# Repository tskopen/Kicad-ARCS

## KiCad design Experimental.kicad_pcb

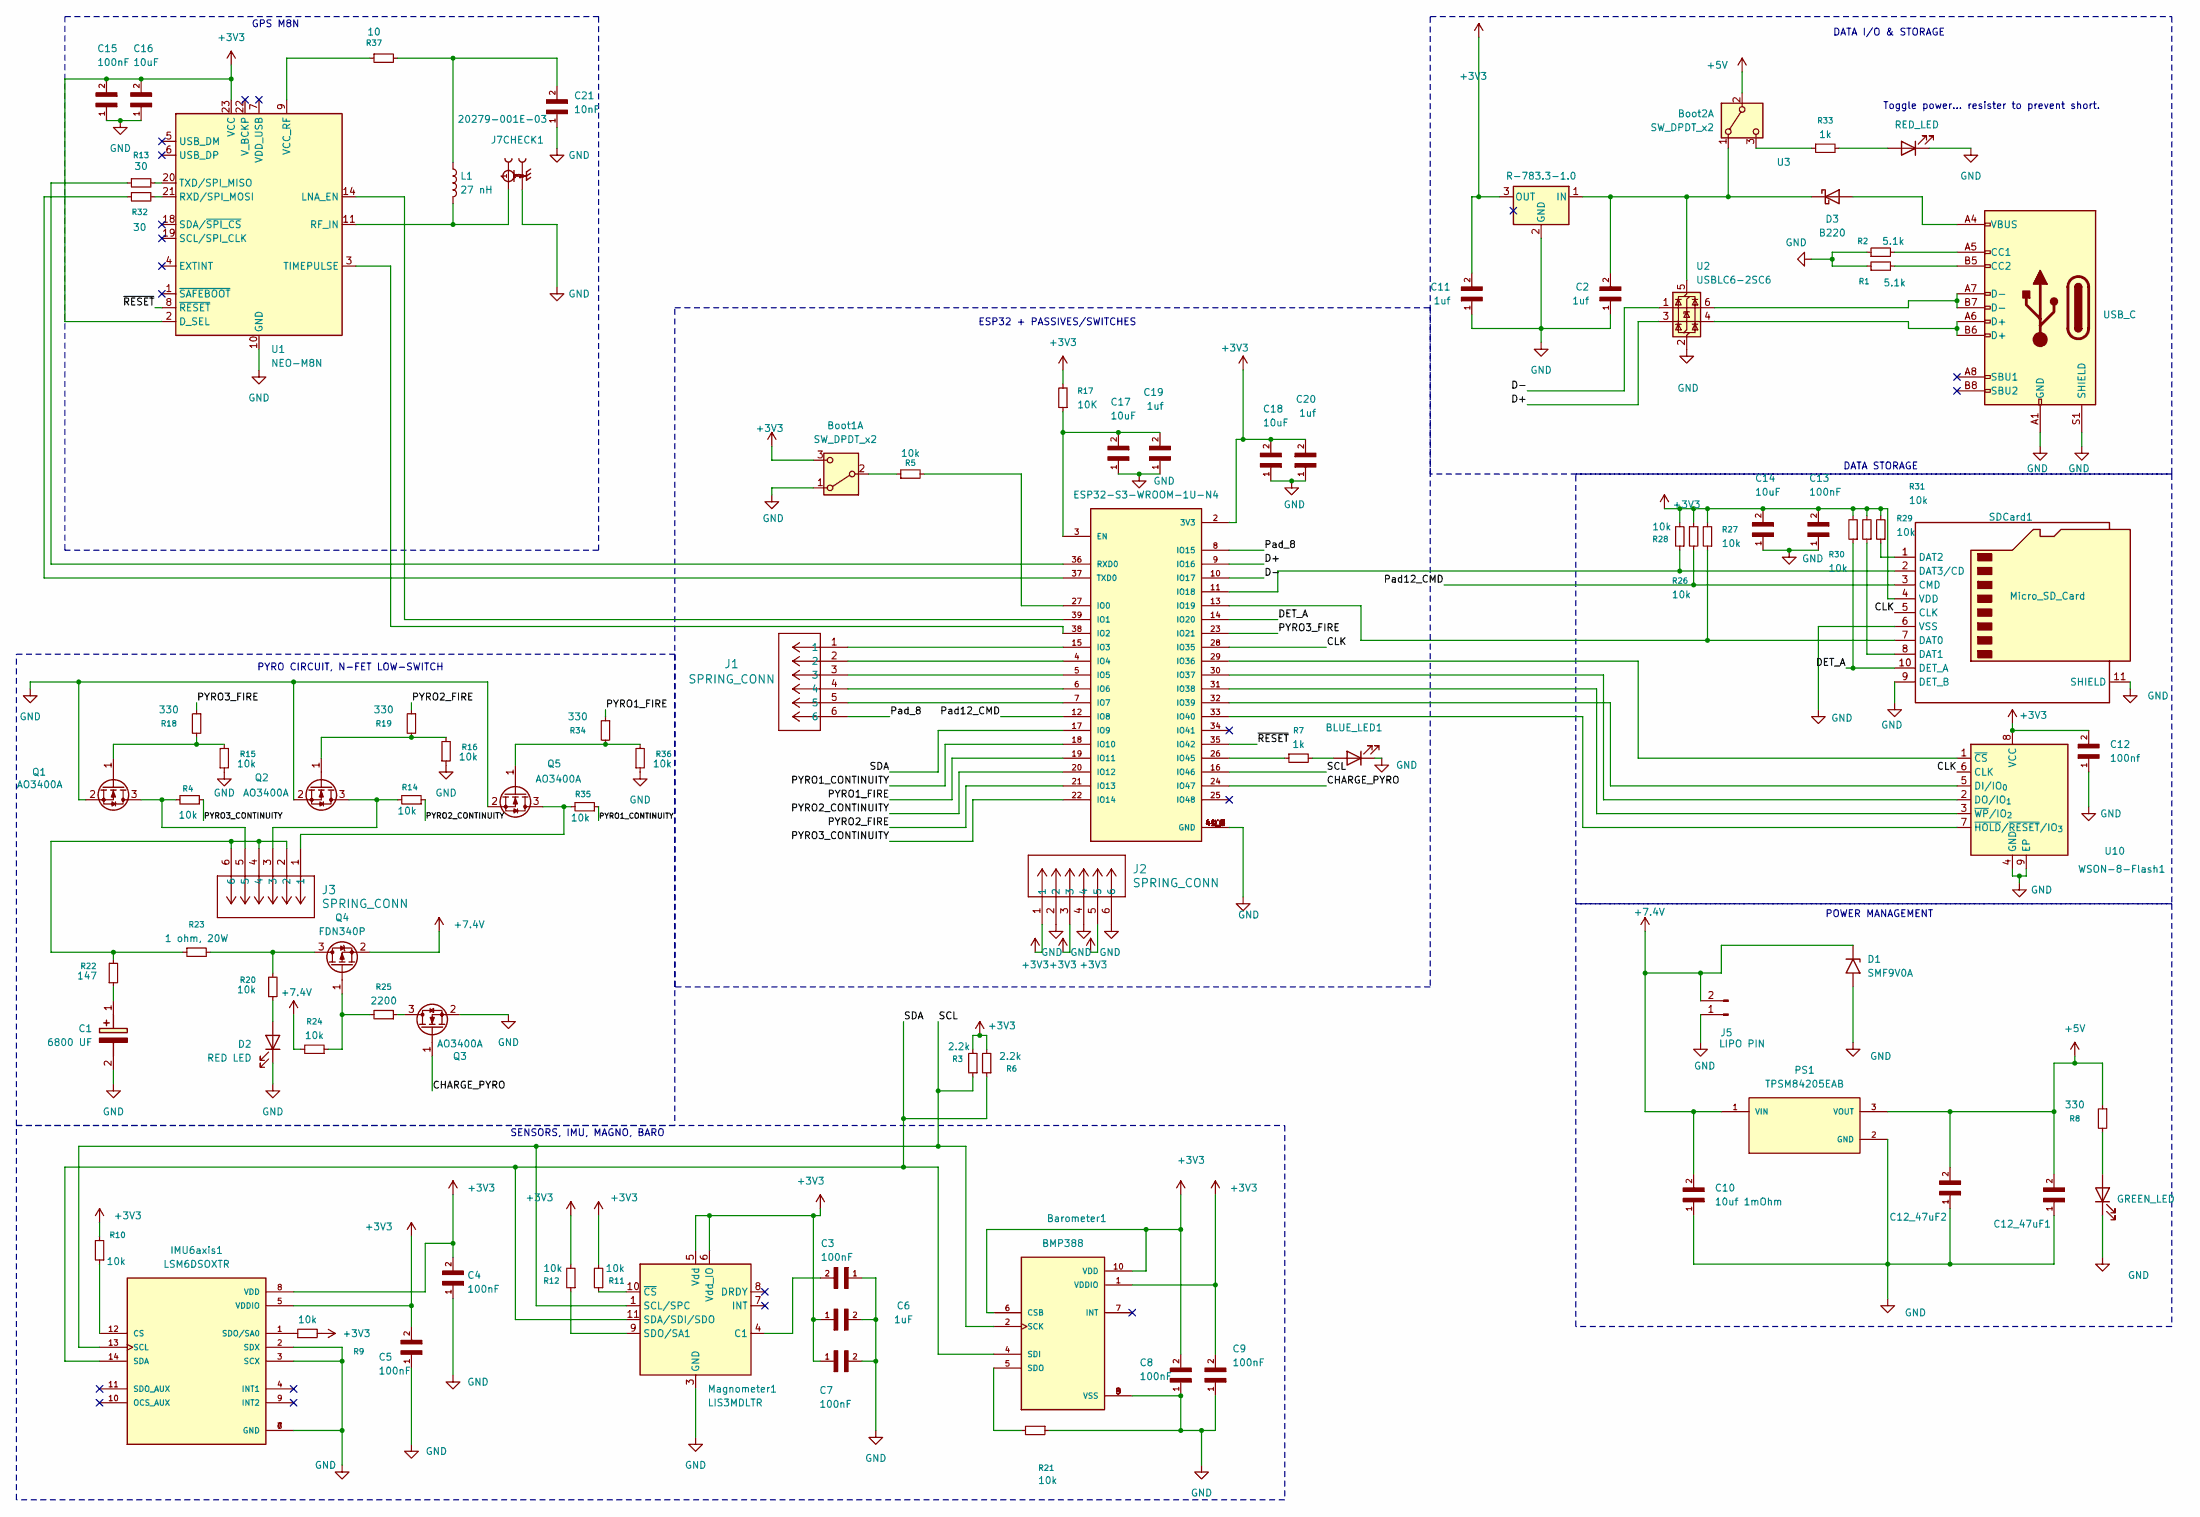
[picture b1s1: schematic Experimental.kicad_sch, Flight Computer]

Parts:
BLUE_LED1: NCD0603G1; LED_0603_1608Metric
Barometer1: BMP388; PQFN50P200X200X80-10N; PARTREV 1.1
Boot1, Boot2: SW_DPDT_x2; SW_DPDT_CK_JS202011JCQN
C1: 6800 UF; CAPPRD500W85D1250H3700; Manufacturer_Part_Number EEU-FR1A682B
C2, C11, C19, C20: 1uf; C_0402_1005Metric; PARTREV NA
C3, C4, C5, C7, C8, C9, C13, C15: 100nF; CAPC1608X90N
C6: 1uF; C_0402_1005Metric; PARTREV NA
C10: 10uf 1mOhm; C_0805_2012Metric; PARTREV NA
C12: 100nf; C_0402_1005Metric; PARTREV NA
C12_47uF1, C12_47uF2: 06034W476MAT2A; C_0201_0603Metric; Mouser Part Number 581-06034W476MAT2A
C14, C16, C17, C18: 10uF; C_0402_1005Metric
C21: 10nF; CAPC1608X90N; PARTREV NA
D1: SMF9V0A; D_SMF
D2: RED LED; LED_0402_1005Metric
D3: B220; D_SMB
ESP32S3: ESP32-S3-WROOM-1U-N4; ESP32-S3-WROOM-1U; PARTREV v0.6
IMU6axis1: LSM6DSOXTR; PQFN50P250X300X86-14N; PARTREV 3.0
J1, J2, J3: SPRING_CONN; 6P_SMD_SPRING_CONN
J5: LIPO PIN; JST_PH_B2B-PH-K_1x02_P2.00mm_Vertical
J7CHECK1: 20279-001E-03; IPEX_20279-001E-03; PARTREV 32
L1: 27 nH; L_0402_1005Metric
Magnometer1: LIS3MDLTR; LGA-12_2x2mm_P0.5mm
NCD0603R1: GREEN_LED; LED_0603_1608Metric
NCD0603R2: RED_LED; LED_0603_1608Metric
PS1: TPSM84205EAB; CONV_TPSM84205EAB
PowerUpload1: USB_C; USB_C_Receptacle_GCT_USB4105-xx-A_16P_TopMnt_Horizontal
Q1, Q2, Q3, Q5: AO3400A; SOT-23
Q4: FDN340P; SOT-23
R1, R2: 5.1k; R0402
R3, R6: 2.2k; R0402
R4, R5, R9, R10, R11, R12, R14, R15, R16, R20, R21, R24, R26, R27, R28, R29, R30, R31, R35, R36: 10k; R0402
R7, R33: 1k; R0402
R8, R18, R19, R34: 330; R0402
R13, R32: 30; R0402
R17: 10K; R0402
R22: 147; R0402
R23: 1 ohm, 20W; R0402
R25: 2200; R0402
R37: 10; R0402
SDCard1: Micro_SD_Card; microSD_HC_Hirose_DM3AT-SF-PEJM5
U1: NEO-M8N; ublox_NEO
U2: USBLC6-2SC6; SOT-23-6
U3: R-783.3-1.0; Converter_DCDC_RECOM_R-78E-0.5_THT
WSON-8-Flash1: U10; WSON-8-1EP_8x6mm_P1.27mm_EP3.4x4.3mm

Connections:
+3V3: Barometer1.1 (VDDIO), Barometer1.6 (CSB), Barometer1.10 (VDD), Boot1.3 (C), C4.2, C5.2, C6.1, C7.1, C8.2, C9.2, C11.2, C12.2, C13.2, C14.2, C15.2, C16.2, C18.2, C20.2, ESP32S3.2 (3V3), IMU6axis1.5 (VDDIO), IMU6axis1.8 (VDD), J2.1, J2.3, J2.5, Magnometer1.5 (Vdd), Magnometer1.6 (Vdd_IO), R3.2, R6.2, R9.2, R10.2, R11.2, R12.2, R17.2, R26.1, R27.2, R28.2, R29.2, R30.2, R31.2, SDCard1.4 (VDD), U1.2 (D_SEL), U1.23 (VCC), U3.3 (OUT), WSON-8-Flash1.8 (VCC)
+5V: Boot2.2 (B), C12_47uF1.2, C12_47uF2.2, PS1.3 (VOUT), R8.1
+7.4V: C10.2, D1.1 (A1), J5.2 (GND), PS1.1 (VIN), Q4.2 (S), R24.2
/CHARGE_PYRO: ESP32S3.24 (IO47), Q3.1 (G)
/CLK: ESP32S3.28 (IO35), SDCard1.5 (CLK), WSON-8-Flash1.6 (CLK)
/D+: ESP32S3.9 (IO16), U2.3 (I/O2)
/D-: ESP32S3.10 (IO17), U2.1 (I/O1)
/DET_A: ESP32S3.14 (IO20), R30.1, SDCard1.10 (DET_A)
/PYRO1_CONTINUITY: ESP32S3.18 (IO10), R35.1
/PYRO1_FIRE: ESP32S3.19 (IO11), R34.1
/PYRO2_CONTINUITY: ESP32S3.20 (IO12), R14.1
/PYRO2_FIRE: ESP32S3.21 (IO13), R19.1
/PYRO3_CONTINUITY: ESP32S3.22 (IO14), R4.1
/PYRO3_FIRE: ESP32S3.23 (IO21), R18.1
/Pad12_CMD: ESP32S3.12 (IO8), R26.2, SDCard1.3 (CMD)
/Pad_8: ESP32S3.8 (IO15), J1.6
/SCL: Barometer1.2 (SCK), ESP32S3.16 (IO46), IMU6axis1.13 (SCL), Magnometer1.1 (SCL/SPC), R3.1
/SDA: Barometer1.4 (SDI), ESP32S3.17 (IO9), IMU6axis1.14 (SDA), Magnometer1.11 (SDA/SDI/SDO), R6.1
/~RESET: ESP32S3.35 (IO42), U1.8 (~RESET)
GND: BLUE_LED1.1 (K), Barometer1.3 (VSS), Barometer1.8 (VSS), Barometer1.9 (VSS), Boot1.1 (A), C1.2 (-), C2.1, C3.1, C4.1, C5.1, C6.2, C7.2, C8.1, C9.1, C10.1, C11.1, C12.1, C12_47uF1.1, C12_47uF2.1, C13.1, C14.1, C15.1, C16.1, C17.1, C18.1, C19.1, C20.1, C21.1, D1.2 (A2), D2.1 (K), ESP32S3.1 (GND), ESP32S3.40 (GND), ESP32S3.41_1 (GND), ESP32S3.41_2 (GND), ESP32S3.41_3 (GND), ESP32S3.41_4 (GND), ESP32S3.41_5 (GND), ESP32S3.41_6 (GND), ESP32S3.41_7 (GND), ESP32S3.41_8 (GND), ESP32S3.41_9 (GND), IMU6axis1.2 (SDX), IMU6axis1.3 (SCX), IMU6axis1.6 (GND), IMU6axis1.7 (GND), J2.2, J2.4, J2.6, J5.1 (7.4v), J7CHECK1.2, J7CHECK1.3, Magnometer1.2 (GND), Magnometer1.3 (GND), Magnometer1.12 (GND), NCD0603R1.1 (K), NCD0603R2.1 (K), PS1.2 (GND), PowerUpload1.A1 (GND), PowerUpload1.A12 (GND), PowerUpload1.B1 (GND), PowerUpload1.B12 (GND), PowerUpload1.S1 (SHIELD), Q1.2 (S), Q2.2 (S), Q3.2 (S), Q5.2 (S), R1.1, R2.1, R15.1, R16.1, R21.1, R36.1, SDCard1.6 (VSS), SDCard1.9 (DET_B), SDCard1.11 (SHIELD), U1.10 (GND), U1.12 (GND), U1.13 (GND), U1.24 (GND), U2.2 (GND), U3.2 (GND), WSON-8-Flash1.4 (GND), WSON-8-Flash1.9 (EP)
unnamed: BLUE_LED1.2 (A), R7.2
unnamed: Barometer1.5 (SDO), R21.2
unnamed: Boot1.2 (B), R5.1
unnamed: Boot2.1 (A), C2.2, D3.1 (K), U2.5 (VBUS), U3.1 (IN)
unnamed: Boot2.3 (C), R33.1
unnamed: C1.1 (+), R22.1
unnamed: C21.2, L1.1, R37.2
unnamed: D2.2 (A), R20.1
unnamed: D3.2 (A), PowerUpload1.A4 (VBUS), PowerUpload1.A9 (VBUS), PowerUpload1.B4 (VBUS), PowerUpload1.B9 (VBUS)
unnamed: C17.2, C19.2, ESP32S3.3 (EN), R17.1
unnamed: ESP32S3.27 (IO0), R5.2
unnamed: ESP32S3.39 (IO1), U1.14 (LNA_EN)
unnamed: ESP32S3.38 (IO2), U1.3 (TIMEPULSE)
unnamed: ESP32S3.15 (IO3), J1.1
unnamed: ESP32S3.4 (IO4), J1.2
unnamed: ESP32S3.5 (IO5), J1.3
unnamed: ESP32S3.6 (IO6), J1.4
unnamed: ESP32S3.7 (IO7), J1.5
unnamed: ESP32S3.11 (IO18), R28.1, SDCard1.2 (DAT3/CD)
unnamed: ESP32S3.13 (IO19), R27.1, SDCard1.7 (DAT0)
unnamed: ESP32S3.29 (IO36), WSON-8-Flash1.1 (~CS)
unnamed: ESP32S3.30 (IO37), WSON-8-Flash1.2 (DO/IO_{1})
unnamed: ESP32S3.31 (IO38), WSON-8-Flash1.3 (~WP/IO_{2})
unnamed: ESP32S3.32 (IO39), WSON-8-Flash1.5 (DI/IO_{0})
unnamed: ESP32S3.33 (IO40), WSON-8-Flash1.7 (~HOLD/~RESET/IO_{3})
unnamed: ESP32S3.26 (IO45), R7.1
unnamed: ESP32S3.36 (RXD0), R13.1
unnamed: ESP32S3.37 (TXD0), R32.1
unnamed: IMU6axis1.12 (CS), R10.1
unnamed: IMU6axis1.1 (SDO/SA0), R9.1
unnamed: J3.2, J3.4, J3.6, R22.2, R23.1
unnamed: C3.2, Magnometer1.4 (C1)
unnamed: Magnometer1.9 (SDO/SA1), R12.1
unnamed: Magnometer1.10 (~CS), R11.1
unnamed: NCD0603R1.2 (A), R8.2
unnamed: NCD0603R2.2 (A), R33.2
unnamed: PowerUpload1.A5 (CC1), R2.2
unnamed: PowerUpload1.B5 (CC2), R1.2
unnamed: PowerUpload1.A6 (D+), PowerUpload1.B6 (D+), U2.4 (I/O2)
unnamed: PowerUpload1.A7 (D-), PowerUpload1.B7 (D-), U2.6 (I/O1)
unnamed: J3.5, Q1.3 (D), R4.2
unnamed: Q1.1 (G), R15.2, R18.2
unnamed: J3.3, Q2.3 (D), R14.2
unnamed: Q2.1 (G), R16.2, R19.2
unnamed: Q3.3 (D), R25.1
unnamed: Q4.3 (D), R20.2, R23.2
unnamed: Q4.1 (G), R24.1, R25.2
unnamed: J3.1, Q5.3 (D), R35.2
unnamed: Q5.1 (G), R34.2, R36.2
unnamed: R29.1, SDCard1.8 (DAT1)
unnamed: R31.1, SDCard1.1 (DAT2)
unnamed: J7CHECK1.1, L1.2, U1.11 (RF_IN)
unnamed: R32.2, U1.21 (RXD/SPI_MOSI)
unnamed: R13.2, U1.20 (TXD/SPI_MISO)
unnamed: R37.1, U1.9 (VCC_RF)

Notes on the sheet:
DATA I/O & STORAGE
DATA STORAGE
GPS M8N
SENSORS, IMU, MAGNO, BARO
PYRO CIRCUIT, N-FET LOW-SWITCH
ESP32 + PASSIVES/SWITCHES
POWER MANAGEMENT
Toggle power... resister to prevent short.

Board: 2 copper layers, 90 parts (0 on the bottom side), 75 nets, no tracks yet.

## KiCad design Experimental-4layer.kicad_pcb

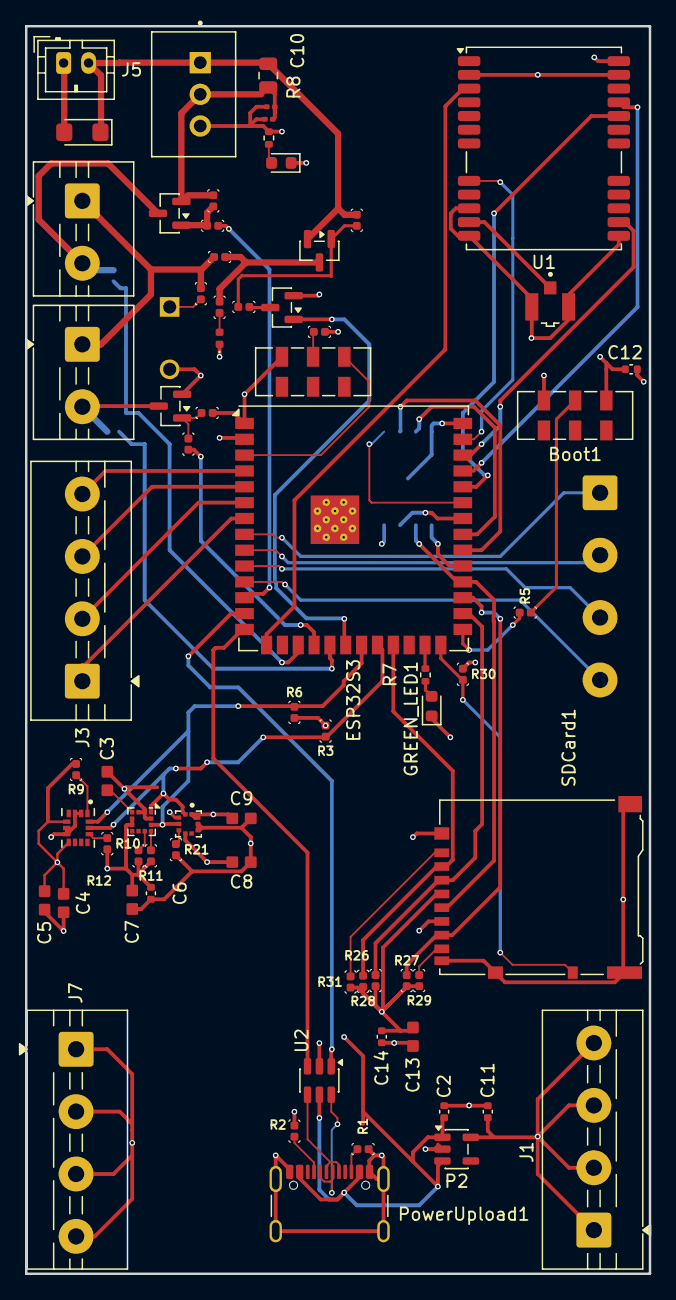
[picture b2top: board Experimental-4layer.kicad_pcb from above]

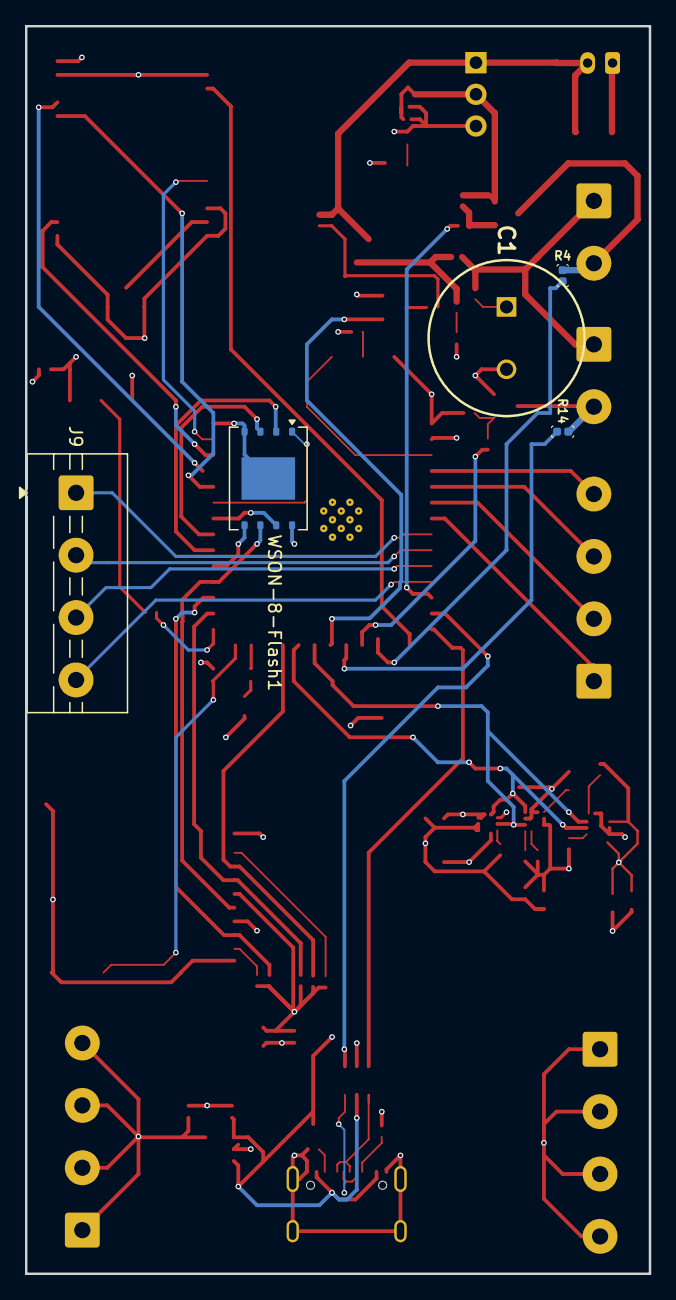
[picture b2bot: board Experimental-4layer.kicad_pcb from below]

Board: 4 copper layers, 50.0 x 100.0 mm, 75 parts (5 on the bottom side), 64 nets.

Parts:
Barometer1: BMP388; PQFN50P200X200X80-10N
Boot1, Boot2: SW_DPDT_x2; SW_DPDT_CK_JS202011JCQN
C1: 6800 UF; CAPPRD500W85D1250H3700
C2, C11: 1uf; C_0402_1005Metric
C3, C4, C5, C7, C8, C9, C13: 100nF; CAPC1608X90N
C6: 1uF; C_0402_1005Metric
C10: 10uf 1mOhm; C_0805_2012Metric
C12: 100nf; C_0402_1005Metric
C12_47uF1, C12_47uF2: 06034W476MAT2A; C_0201_0603Metric
C14: 10uF; C_0402_1005Metric
D1: SMF9V0A; D_SMF
D2: RED LED; LED_0402_1005Metric
ESP32S3: ESP32-S3-WROOM-1U-N4; ESP32-S3-WROOM-1U
GREEN_LED1: NCD0603G1; LED_0603_1608Metric
IMU6axis1: LSM6DSOXTR; PQFN50P250X300X86-14N
J1, J3, J7, J9: MX128-5.0-04P-GN01-Cu-Y-A; TerminalBlock_MaiXu_MX126-5.0-04P_1x04_P5.00mm
J2, J10: Screw_Terminal; TerminalBlock_MaiXu_MX126-5.0-02P_1x02_P5.00mm
J5: LIPO PIN; JST_PH_B2B-PH-K_1x02_P2.00mm_Vertical
J7CHECK1: 20279-001E-03; IPEX_20279-001E-03
Magnometer1: LIS3MDLTR; LGA-12_2x2mm_P0.5mm
NCD0603R1: RED_LED; LED_0603_1608Metric
P2: LP5907MFX-3.3; SOT-23-5
PS1: TPSM84205EAB; CONV_TPSM84205EAB
PowerUpload1: USB_C; USB_C_Receptacle_GCT_USB4105-xx-A_16P_TopMnt_Horizontal
Q1, Q2, Q3: AO3400A; SOT-23
Q4: FDN340P; SOT-23
R1, R2: 5.1k; R0402
R3, R6: 2.2k; R0402
R4, R5, R9, R10, R11, R12, R14, R15, R16, R20, R21, R24, R26, R27, R28, R29, R30, R31: 10k; R0402
R7, R8: 5.4k; R_0402_1005Metric
R17: 10K; R0402
R18, R19: 330; R0402
R22: 147; R0402
R23: 1 ohm, 20W; R0402
R25: 2200; R0402
SDCard1: Micro_SD_Card; microSD_HC_Hirose_DM3AT-SF-PEJM5
U1: NEO-M8N; ublox_NEO
U2: USBLC6-2SC6; SOT-23-6
WSON-8-Flash1: U10; WSON-8-1EP_8x6mm_P1.27mm_EP3.4x4.3mm

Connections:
+3V3: Barometer1.1 (VDDIO), Barometer1.6 (CSB), Barometer1.10 (VDD), Boot1.3 (C), C4.2, C5.2, C6.1, C7.1, C8.1, C9.1, C11.2, C12.2, C13.2, C14.2, ESP32S3.2 (3V3), IMU6axis1.5 (VDDIO), IMU6axis1.8 (VDD), J1.1, J1.2, J1.3, J1.4, Magnometer1.5 (Vdd), Magnometer1.6 (Vdd_IO), P2.5 (OUT), R3.2, R6.2, R9.2, R10.2, R11.2, R12.2, R17.2, R26.1, R27.2, R28.2, R29.2, R30.2, R31.2, SDCard1.4 (VDD), U1.2 (D_SEL), U1.23 (VCC), WSON-8-Flash1.8 (VCC)
+5V: C2.2, C12_47uF1.2, C12_47uF2.2, P2.1 (IN), P2.3 (EN), PS1.3 (VOUT), PowerUpload1.A4 (VBUS), PowerUpload1.A9 (VBUS), PowerUpload1.B4 (VBUS), PowerUpload1.B9 (VBUS), R8.1, U2.5 (VBUS)
+7.4V: C10.2, D1.1 (A1), J5.2 (GND), PS1.1 (VIN), Q4.2 (S), R24.2
/CHARGE_PYRO: ESP32S3.20 (IO12), Q3.1 (G)
/CS_FLASH: ESP32S3.35 (IO42), WSON-8-Flash1.1 (~CS)
/DET_A: ESP32S3.26 (IO45), R30.1, SDCard1.10 (DET_A)
/PYRO2_FIRE: ESP32S3.12 (IO8), R18.1
/PYRO_FIRE: ESP32S3.18 (IO10), R19.1
/~RESET: ESP32S3.39 (IO1), U1.8 (~RESET)
GND: Barometer1.3 (VSS), Barometer1.8 (VSS), Barometer1.9 (VSS), Boot1.1 (A), Boot2.1 (A), C1.2 (-), C2.1, C3.2, C4.1, C5.1, C6.2, C7.2, C8.2, C9.2, C10.1, C11.1, C12.1, C12_47uF1.1, C12_47uF2.1, C13.1, C14.1, D1.2 (A2), D2.1 (K), ESP32S3.1 (GND), ESP32S3.17 (IO9), ESP32S3.19 (IO11), ESP32S3.40 (GND), GREEN_LED1.1 (K), IMU6axis1.2 (SDX), IMU6axis1.3 (SCX), IMU6axis1.6 (GND), IMU6axis1.7 (GND), J5.1 (7.4v), J7.1, J7.2, J7.3, J7.4, J7CHECK1.2, J7CHECK1.3, Magnometer1.2 (GND), Magnometer1.3 (GND), Magnometer1.12 (GND), NCD0603R1.1 (K), P2.2 (GND), PS1.2 (GND), PowerUpload1.A1 (GND), PowerUpload1.A12 (GND), PowerUpload1.B1 (GND), PowerUpload1.B12 (GND), PowerUpload1.S1 (SHIELD), Q1.2 (S), Q2.2 (S), Q3.2 (S), R1.1, R2.1, R4.1, R14.1, R15.1, R16.1, R21.1, SDCard1.6 (VSS), SDCard1.9 (DET_B), SDCard1.11 (SHIELD), U1.10 (GND), U1.12 (GND), U1.13 (GND), U1.24 (GND), U2.2 (GND), WSON-8-Flash1.4 (GND), WSON-8-Flash1.9 (EP)
unnamed: Barometer1.2 (SCK), ESP32S3.22 (IO14), IMU6axis1.13 (SCL), Magnometer1.1 (SCL/SPC), R3.1
unnamed: Barometer1.4 (SDI), ESP32S3.21 (IO13), IMU6axis1.14 (SDA), Magnometer1.11 (SDA/SDI/SDO), R6.1
unnamed: Barometer1.5 (SDO), R21.2
unnamed: Boot1.2 (B), R5.1
unnamed: Boot2.2 (B), R17.1
unnamed: Boot2.3 (C), ESP32S3.3 (EN)
unnamed: C1.1 (+), R22.1
unnamed: D2.2 (A), R20.1
unnamed: ESP32S3.27 (IO0), R5.2
unnamed: ESP32S3.38 (IO2), U1.14 (LNA_EN)
unnamed: ESP32S3.15 (IO3), U1.3 (TIMEPULSE)
unnamed: ESP32S3.4 (IO4), J3.4
unnamed: ESP32S3.5 (IO5), J3.3
unnamed: ESP32S3.6 (IO6), J3.2
unnamed: ESP32S3.7 (IO7), J3.1
unnamed: ESP32S3.8 (IO15), J9.1
unnamed: ESP32S3.9 (IO16), J9.2
unnamed: ESP32S3.10 (IO17), J9.3
unnamed: ESP32S3.11 (IO18), J9.4
unnamed: ESP32S3.13 (IO19), U2.1 (I/O1)
unnamed: ESP32S3.14 (IO20), U2.3 (I/O2)
unnamed: ESP32S3.23 (IO21), R28.1, SDCard1.2 (DAT3/CD)
unnamed: ESP32S3.28 (IO35), R26.2, SDCard1.3 (CMD)
unnamed: ESP32S3.29 (IO36), R27.1, SDCard1.7 (DAT0)
unnamed: ESP32S3.30 (IO37), SDCard1.5 (CLK), WSON-8-Flash1.6 (CLK)
unnamed: ESP32S3.31 (IO38), WSON-8-Flash1.5 (DI/IO_{0})
unnamed: ESP32S3.32 (IO39), WSON-8-Flash1.2 (DO/IO_{1})
unnamed: ESP32S3.33 (IO40), WSON-8-Flash1.3 (~WP/IO_{2})
unnamed: ESP32S3.34 (IO41), WSON-8-Flash1.7 (~HOLD/~RESET/IO_{3})
unnamed: ESP32S3.25 (IO48), R7.1
unnamed: ESP32S3.36 (RXD0), U1.20 (TXD/SPI_MISO)
unnamed: ESP32S3.37 (TXD0), U1.21 (RXD/SPI_MOSI)
unnamed: GREEN_LED1.2 (A), R7.2
unnamed: IMU6axis1.12 (CS), R10.1
unnamed: IMU6axis1.1 (SDO/SA0), R9.1
unnamed: J2.2, Q2.3 (D), R14.2
unnamed: J2.1, J10.1, R22.2, R23.1
unnamed: J10.2, Q1.3 (D), R4.2
unnamed: C3.1, Magnometer1.4 (C1)
unnamed: Magnometer1.9 (SDO/SA1), R12.1
unnamed: Magnometer1.10 (~CS), R11.1
unnamed: NCD0603R1.2 (A), R8.2
unnamed: PowerUpload1.A5 (CC1), R2.2
unnamed: PowerUpload1.B5 (CC2), R1.2
unnamed: PowerUpload1.A6 (D+), PowerUpload1.B6 (D+), U2.4 (I/O2)
unnamed: PowerUpload1.A7 (D-), PowerUpload1.B7 (D-), U2.6 (I/O1)
unnamed: Q1.1 (G), R15.2, R18.2
unnamed: Q2.1 (G), R16.2, R19.2
unnamed: Q3.3 (D), R25.1
unnamed: Q4.3 (D), R20.2, R23.2
unnamed: Q4.1 (G), R24.1, R25.2
unnamed: R29.1, SDCard1.8 (DAT1)
unnamed: R31.1, SDCard1.1 (DAT2)
unnamed: J7CHECK1.1, U1.11 (RF_IN)

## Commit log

2025-12-22 Inital commit
2025-12-24 Revision
2025-12-28 update Schematic
    Fixed N channel mosfet pyros and set to low side trigger
    removed unneeded 5v buck converter
    rerouted/optmized gpio pins
2025-12-29 Upload libraries for portability
2025-12-29 Tweaks and readability
2025-12-30 Undo hiearchical layer
2025-12-31 scratch
2026-01-01 Schematic Revision v4
2026-01-02 Version 4.0
    Schematic Cleanup and PCB Layout/Impletementation
2026-01-04 Version 5.0!
